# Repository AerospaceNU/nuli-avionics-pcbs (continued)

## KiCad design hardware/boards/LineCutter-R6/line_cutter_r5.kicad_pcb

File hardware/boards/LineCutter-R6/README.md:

# LineCutter-R6

Line cutter, revision 6 (project files are still named r5).

## Contributors

Patrick McGuire, zilinSi

## Status

**Version:** not recorded (the board's title block has no revision)
**Status:** Moved here from CADLab NULIAvionics/Line-Cutters-R6; this folder is now the working copy.

## Description

Line cutter, revision 6 (project files are still named r5).

- KiCad project: `line_cutter_r5.kicad_pro`, last saved with KiCad 7.0
- Schematic sheets: `line_cutter_r5.kicad_sch`, `storage.kicad_sch`, `power.kicad_sch`, `input_prot.kicad_sch`, `mcu.kicad_sch`, `sensors.kicad_sch`, `usb_hub.kicad_sch`, `pyros_servos.kicad_sch`, `pyro_chan.kicad_sch`
- Board size: 61.1 x 30.6 mm
- `fabrication/`: `assembly/`, `bom/`, `gerbers/`, `pick-and-place/`

## Manufacturing

- Layers: 4
- Thickness: 1.606 mm
- Surface finish: not set in the board stackup
- Minimum trace/space: 0.127 mm / 0.127 mm (smallest track on the board / default netclass clearance)
- Minimum drill: 0.305 mm (design rule)
- Manufacturer: not recorded

## Known Issues

- The schematic and PCB are out of sync: 21 parts have a different footprint on the PCB than in the schematic, and 23 schematic parts aren't on the PCB. Run Update PCB from Schematic before the next spin.
- Its library tables also point at `../fcb_v2_lib.kicad_sym` and `../fcb_footprints.pretty`, which weren't in the CADLab repo.

## Revision History

| Version | Date | Changes |
|---|---|---|
| - | 2024-12-06 | Moved into this repo from CADLab NULIAvionics/Line-Cutters-R6 (history from 2024-11-14 to 2024-12-06 stays there) |

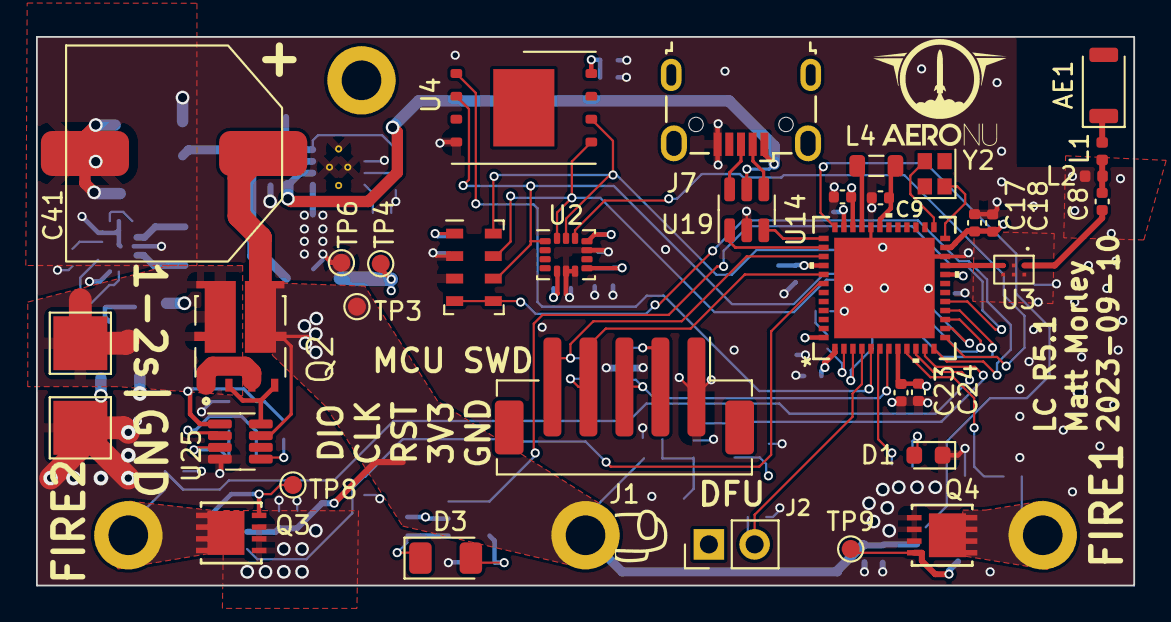
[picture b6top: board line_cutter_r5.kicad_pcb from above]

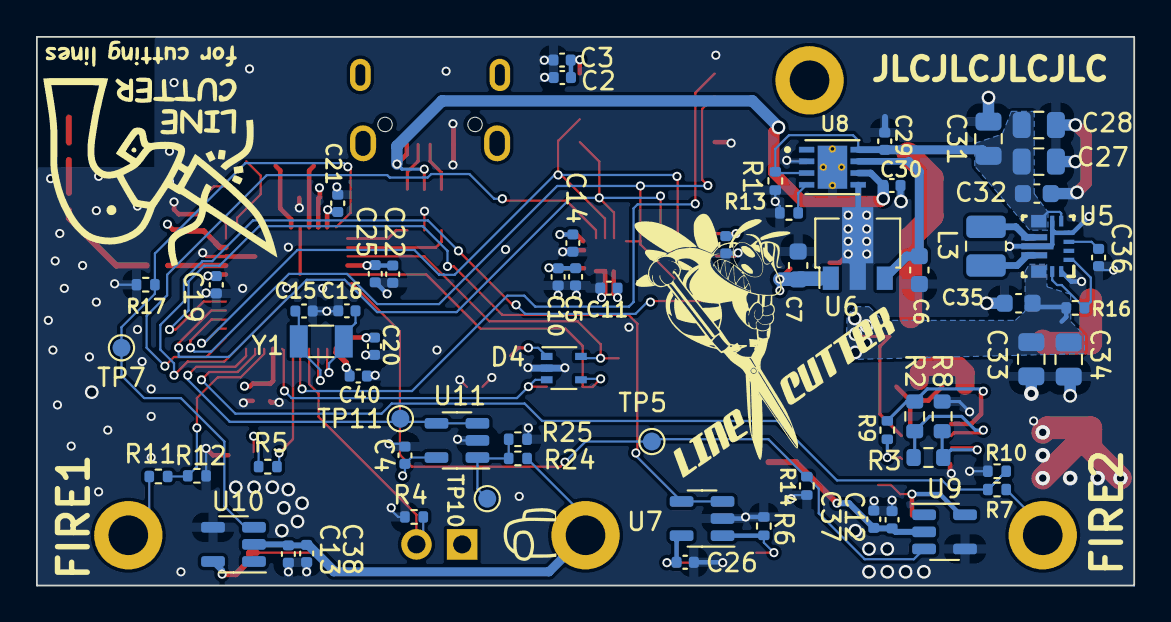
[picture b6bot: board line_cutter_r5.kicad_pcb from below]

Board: 4 copper layers, 61.0 x 30.5 mm, 104 parts (65 on the bottom side), 56 nets.

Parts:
AE1: 2450AT18B0100001E; Johanson_2450AT18x100_fixed
C1, C3, C4, C10, C12, C13, C14, C26, C29, C30, C36: 0.1u; C_0402_1005Metric
C2, C24, C37, C38: 1u; C_0402_1005Metric
C5: 2.2u; C_0402_1005Metric
C6: 1u; C_0603_1608Metric
C7: 4.7u; C_0603_1608Metric
C8: 1.2p; C_0402_1005Metric
C9, C22, C39: 4.7u; C_0402_1005Metric
C11, C23: 10n; C_0402_1005Metric
C15, C16: 15p; C_0402_1005Metric
C17, C19, C20, C21, C25, C40: 100n; C_0402_1005Metric
C18: 100p; C_0402_1005Metric
C27, C28, C31: 22u; C_0805_2012Metric
C32, C35: 10u; C_0603_1608Metric
C33, C34: 10u; C_0805_2012Metric
C41: 100m; FCS0H104ZFTBR24
D1: LED_Small; LED_0603_1608Metric
D3: PDB-C152SM; D_1206_3216Metric
D4: PESD3V3L4UG; SOT-353_SC-70-5
H1, H5, H6, H7: MountingHole_Pad; MountingHole_2.2mm_M2_DIN965_Pad
J1: Conn_01x05; JST_PH_B5B-PH-SM4-TB_1x05-1MP_P2.00mm_Vertical
J2: Conn_01x02_Female; PinHeader_1x02_P2.54mm_Vertical
J7: USB_B_Micro; USB_Micro-B_Wuerth_629105150521
L1: 3.3n; L_0402_1005Metric
L2: 2.7n; L_0402_1005Metric
L3: 1.5u; L_1008_2520Metric
L4: 2.2u; L_0805_2012Metric
Q2: SQJ974EP-T1_GE3; TRANS_SQJ974EP-T1_GE3
Q3, Q4: AON7528; DFN3X3A_8L_EPA1_P_AOS
R1, R10, R12, R14, R16, R17, R25: 10k; R_0402_1005Metric
R2: 320k; R_0603_1608Metric
R3: 270k; R_0603_1608Metric
R4, R9: 100k; R_0402_1005Metric
R5: 2k; R_0402_1005Metric
R6: 160k; R_0402_1005Metric
R7, R11, R24: 20k; R_0402_1005Metric
R8: 30k; R_0603_1608Metric
R13: 402R; R_0402_1005Metric
TP1, TP2: TestPoint; TestPoint_Pad_3.0x3.0mm
TP3, TP4, TP5, TP6, TP7, TP8, TP9, TP10, TP11: TestPoint; TestPoint_Pad_D1.0mm
U1: MS5607-02BA; LGA-8_3x5mm_P1.25mm
U2: ICM-20600; LGA-14_3x2.5mm_P0.5mm_LayoutBorder3x4y
U3: MLPF-WB55-01E3; MLPF-WB55-01E3_STM
U4: S25fl256lagnfi010; WSON-8-1EP_8x6mm_P1.27mm_EP3.4x4.3mm
U5: TPS630701RNMR; RNM0015A
U6: C50936; SOT-89-3
U7, U11: LMV321; SOT-23-5
U8: TPS2115ADRBR; SON65P300X300X100-9N
U9, U10: MCP1416; SOT-23-5
U14: STM32WB55CCU6TR; UFQFPN48-7x7mm
U19: USBLC6-2SC6; SOT-23-6
U25: LTC4365xTS8; TSOT-23-8
Y1: Q13FC1350000400; Crystal_SMD_3215-2Pin_3.2x1.5mm
Y2: ECS-320-8-37CKM; Crystal_SMD_2016-4Pin_2.0x1.6mm

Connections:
+3V3: C1.1, C2.2, C3.2, C4.1, C5.1, C7.1, C10.1, C11.1, C17.2, C18.2, C19.1, C20.1, C21.1, C22.1, C23.1, C24.1, C25.1, C26.1, C39.1, C40.2, D3.2 (A), D4.1 (K1), J1.2, J2.1, TP4.1, U1.1 (VDD), U2.5 (VDDIO), U2.8 (VDD), U4.8 (VCC), U6.1 (VOUT), U7.5 (V+), U11.5 (V+), U14.1 (VBAT), U14.8 (VDDA), U14.20 (VDD), U14.23 (VDDRF), U14.34 (VDDSMPS), U14.35 (VDD), U14.40 (VDDUSB), U14.48 (VDD)
+5V: C6.1, U6.3 (VIN), U8.7 (OUT)
/Main MCU/BARO1_CS: U1.4 (CSB), U1.5 (CSB), U14.12 (PA3)
/Main MCU/BOOT0: J2.2, R4.1, U14.4 (PH3-BOOT0)
/Main MCU/FCB_SWCLK: D4.4 (K3), J1.4, U14.41 (PA14)
/Main MCU/FCB_SWDIO: D4.5 (K4), J1.5, U14.39 (PA13)
/Main MCU/FIRE1_PWM: R17.2, TP7.1, U10.3 (IN), U14.36 (PA10)
/Main MCU/FIRE2_PWM: R14.2, TP5.1, U9.3 (IN), U14.42 (PA15)
/Main MCU/FLASH_CS: U4.1 (nCS), U14.5 (PB8)
/Main MCU/IMU1_CS: U2.12 (~CS), U14.13 (PA4)
/Main MCU/LIGHT_SENSE_BUF: U7.3 (-), U7.4, U14.17 (PA8)
/Main MCU/PYRO_SENSE_1: R11.1, R12.2, U14.9 (PA0)
/Main MCU/PYRO_SENSE_2: R7.1, R10.2, U14.10 (PA1)
/Main MCU/SPI_MISO: U1.6 (SDO), U2.1 (SDO/AD0), U4.2 (SO/IO1), U14.15 (PA6)
/Main MCU/SPI_MOSI: U1.7 (SDI/SDA), U2.14 (SDA/SDI), U4.5 (SI/IO0), U14.16 (PA7)
/Main MCU/SPI_SCK: U1.8 (SCLK), U2.13 (SCL/SCLK), U4.6 (SCK), U14.14 (PA5)
/Main MCU/STM_RF1_50R: U3.3 (IN), U14.21 (RF1)
/Main MCU/STM_RF2_50R: C8.1, U3.1 (OUT)
/Main MCU/STM_RF3_50R: C8.2, L1.2, L2.1
/Main MCU/STM_RF4_50R: AE1.1 (FEED), L1.1
/Main MCU/USB_D+: U14.38 (PA12), U19.1 (I/O1)
/Main MCU/USB_D-: U14.37 (PA11), U19.3 (I/O2)
/Main MCU/USER_LED: R5.2, U14.6 (PB9)
/Main MCU/VBATT_SENSE_IN: TP11.1, U11.3 (-), U11.4, U14.11 (PA2)
/Main MCU/nRST: D4.3 (K2), J1.3, U14.7 (NRST)
/Power Supplies/5V_BUCK-BOOST: C27.2, C28.2, C29.2, C31.2, C32.2, R1.1, U5.5 (FB), U5.7 (VOUT), U5.8 (VOUT), U8.3 (D1), U8.8 (IN1)
/Power Supplies/BATT_IN: C12.1, C13.1, C33.2, C34.2, C35.2, C37.1, C38.1, C41.1, H6.1, Q2.5, Q2.5_1, Q2.5_2, R16.2, R24.1, TP3.1, U5.12 (VIN), U5.13 (VIN), U9.2 (Vdd), U10.2 (Vdd), U25.7 (VOUT)
/Power Supplies/Input Protection/VIN: Q2.6, Q2.6_1, Q2.6_2, R2.2, R9.1, TP1.1, U25.1 (VIN)
/Power Supplies/USB_5V_IN: C30.2, J7.1 (VBUS), U8.6 (IN2), U19.5 (VBUS)
/Power Supplies/VBATT_SENSE: R24.2, R25.1, TP10.1, U11.1 (+)
/Pyros and Servos/PYRO1: H5.1, Q4.5 (D), Q4.6 (D), Q4.7 (D), Q4.8 (D), Q4.9 (D), R11.2
/Pyros and Servos/PYRO2: H7.1, Q3.5 (D), Q3.6 (D), Q3.7 (D), Q3.8 (D), Q3.9 (D), R7.2
/Pyros and Servos/Pyro Channel1/GATE: Q3.4 (G), TP8.1, U9.5 (OUT)
/Pyros and Servos/Pyro Channel/GATE: Q4.4 (G), TP9.1, U10.5 (OUT)
/USB Hub/UFP_D+: J7.3 (D+), U19.6 (I/O1)
/USB Hub/UFP_D-: J7.2 (D-), U19.4 (I/O2)
GND: C1.2, C2.1, C3.1, C4.2, C5.2, C6.2, C7.2, C9.2, C10.2, C11.2, C12.2, C13.2, C14.2, C15.1, C16.1, C17.1, C18.1, C19.2, C20.2, C21.2, C22.2, C23.2, C24.2, C25.2, C26.2, C27.1, C28.1, C29.1, C30.1, C31.1, C32.1, C33.1, C34.1, C35.1, C36.1, C37.2, C38.2, C39.2, C40.1, C41.2, D1.1 (K), D4.2 (A), J1.1, J7.5 (GND), L2.2, Q3.1 (S), Q3.2 (S), Q3.3 (S), Q4.1 (S), Q4.2 (S), Q4.3 (S), R1.2, R4.2, R6.2, R8.1, R10.1, R12.1, R13.1, R14.1, R17.1, R25.2, TP2.1, TP6.1, U1.2 (PS), U1.3 (GND), U2.6 (GND), U2.7 (RESV), U2.10 (FSYNC), U3.2 (GND), U3.4 (GND), U3.5 (GND), U3.6 (GND), U4.4 (GND), U5.4 (GND), U5.6 (FB2), U5.10 (PGND), U5.15 (VSEL), U6.2 (GND), U7.2 (V-), U8.2 (D0), U8.5 (GND), U8.9 (GND), U8.10 (GND), U9.4 (GND), U10.4 (GND), U11.2 (V-), U14.22 (VSSRF), U14.32 (VSSSMPS), U14.49 (EPAD), U19.2 (GND), U25.4 (GND)
unnamed: D1.2 (A), R5.1
unnamed: D3.1 (K), R6.1, U7.1 (+)
unnamed: Q2.1, Q2.3
unnamed: C14.1, U2.11 (REGOUT)
unnamed: R16.1, U5.1 (PS_SYNC), U5.14 (EN)
unnamed: L3.1, U5.11 (L1)
unnamed: L3.2, U5.9 (L2)
unnamed: C36.2, U5.3 (VAUX)
unnamed: R13.2, U8.4 (ILIM)
unnamed: U14.25 (OSC_IN), Y2.3
unnamed: U14.24 (OSC_OUT), Y2.1
unnamed: C16.2, U14.2 (PC14-OSC32_IN), Y1.1
unnamed: C15.2, U14.3 (PC15-OSC32_OUT), Y1.2
unnamed: C9.1, L4.2, U14.31 (VFBSMPS)
unnamed: L4.1, U14.33 (VLXSMPS)
unnamed: Q2.2, Q2.4, U25.8 (GATE)
unnamed: R3.1, R8.2, U25.3 (OV)
unnamed: R2.1, R3.2, U25.2 (UV)
unnamed: R9.2, U25.5 (~SHDN)

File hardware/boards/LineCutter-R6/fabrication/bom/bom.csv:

Designator,Footprint,Quantity,Value,LCSC Part #
AE1,Johanson_2450AT18x100_fixed,1,2450AT18B0100001E,
"C1, C10, C12, C13, C14, C26, C29, C3, C30, C36, C4",0402,11,0.1u,
"C11, C23",0402,2,10n,
"C15, C16",0402,2,15p,
"C17, C19, C20, C21, C25, C40",0402,6,100n,
C18,0402,1,100p,
"C2, C24, C37, C38",0402,4,1u,
"C22, C39, C9",0402,3,4.7u,
"C27, C28, C31",0805,3,22u,
"C32, C35",0603,2,10u,
"C33, C34",0805,2,10u,
C41,FCS0H104ZFTBR24,1,100m,
C5,0402,1,2.2u,
C6,0603,1,1u,
C7,0603,1,4.7u,
C8,0402,1,1.2p,
D1,0603,1,LED_Small,
D3,1206,1,PDB-C152SM,
D4,SOT-353_SC-70-5,1,PESD3V3L4UG,
"H1, H5, H6, H7",MountingHole_2.2mm_M2_DIN965_Pad,4,MountingHole_Pad,
J1,JST_PH_B5B-PH-SM4-TB_1x05-1MP_P2.00mm_Vertical,1,Conn_01x05,
J2,PinHeader_1x02_P2.54mm_Vertical,1,Conn_01x02_Female,
J7,USB_Micro-B_Wuerth_629105150521,1,USB_B_Micro,
L1,0402,1,3.3n,
L2,0402,1,2.7n,
L3,1008,1,1.5u,DFE252012F-1R5M=P2
L4,0805,1,2.2u,
Q2,TRANS_SQJ974EP-T1_GE3,1,SQJ974EP-T1_GE3,
"Q3, Q4",DFN3X3A_8L_EPA1_P_AOS,2,AON7528,
"R1, R10, R12, R14, R16, R17, R25",0402,7,10k,
"R11, R24, R7",0402,3,20k,
R13,0402,1,402R,
R2,0603,1,320k,
R3,0603,1,270k,
"R4, R9",0402,2,100k,
R5,0402,1,2k,
R6,0402,1,160k,
R8,0603,1,30k,
"TP1, TP2",TestPoint_Pad_3.0x3.0mm,2,TestPoint,
"TP10, TP11, TP3, TP4, TP5, TP6, TP7, TP8, TP9",TestPoint_Pad_D1.0mm,9,TestPoint,
U1,LGA-8_3x5mm_P1.25mm,1,MS5607-02BA,
"U10, U9",SOT-23-5,2,MCP1416,
"U11, U7",SOT-23-5,2,LMV321,
U14,UFQFPN48-7x7mm,1,STM32WB55CCU6TR,
U19,SOT-23-6,1,USBLC6-2SC6,
U2,LGA-14_3x2.5mm_P0.5mm_LayoutBorder3x4y,1,ICM-20600,
U25,TSOT-23-8,1,LTC4365xTS8,
U3,MLPF-WB55-01E3_STM,1,MLPF-WB55-01E3,
U4,WSON-8-1EP_8x6mm_P1.27mm_EP3.4x4.3mm,1,S25fl256lagnfi010,
U5,RNM0015A,1,TPS630701RNMR,
U6,SOT-89-3,1,C50936,
U8,SON65P300X300X100-9N,1,TPS2115ADRBR,
Y1,Crystal_SMD_3215-2Pin_3.2x1.5mm,1,Q13FC1350000400,
Y2,Crystal_SMD_2016-4Pin_2.0x1.6mm,1,ECS-320-8-37CKM,

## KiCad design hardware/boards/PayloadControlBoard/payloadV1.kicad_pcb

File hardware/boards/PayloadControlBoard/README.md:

# PayloadControlBoard

Payload control board V1.

## Contributors

Patrick McGuire, Riley Post

## Status

**Version:** not recorded (the board's title block has no revision)
**Status:** Moved here from CADLab NULIAvionics/Payload-Control-Board; this folder is now the working copy.

## Description

Payload control board V1.

- KiCad project: `payloadV1.kicad_pro`, last saved with KiCad 8.0
- Schematic sheets: `payloadV1.kicad_sch`
- Board size: 77.8 x 52.3 mm
- `3d-models/`: board STEP export
- `fabrication/`: `bom/`, `drill/`, `gerbers/`, `pick-and-place/`

## Manufacturing

- Layers: 4
- Thickness: 1.6 mm
- Surface finish: not set in the board stackup
- Minimum trace/space: 0.157 mm / 0.2 mm (smallest track on the board / default netclass clearance)
- Minimum drill: 0.3 mm (design rule)
- Manufacturer: JLCPCB (the fabrication outputs are JLCPCB's)

## Known Issues

- Its library tables point at another machine's folders, so KiCad warns about missing libraries; the symbols and footprints stored in the design still open fine, and the parts are in `hardware/common-components/`.

## Revision History

| Version | Date | Changes |
|---|---|---|
| - | 2025-05-23 | Moved into this repo from CADLab NULIAvionics/Payload-Control-Board (history from 2024-12-06 to 2025-05-23 stays there) |

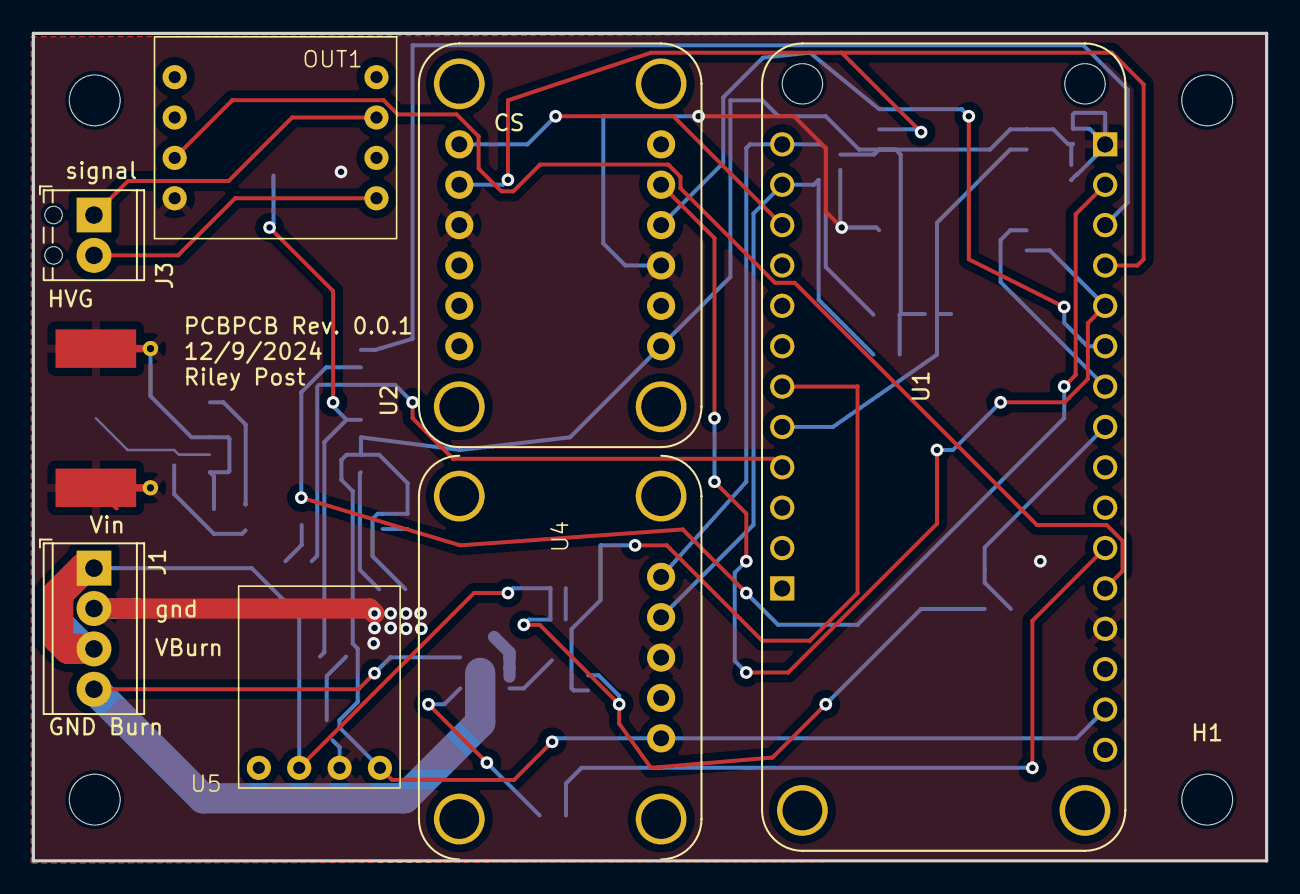
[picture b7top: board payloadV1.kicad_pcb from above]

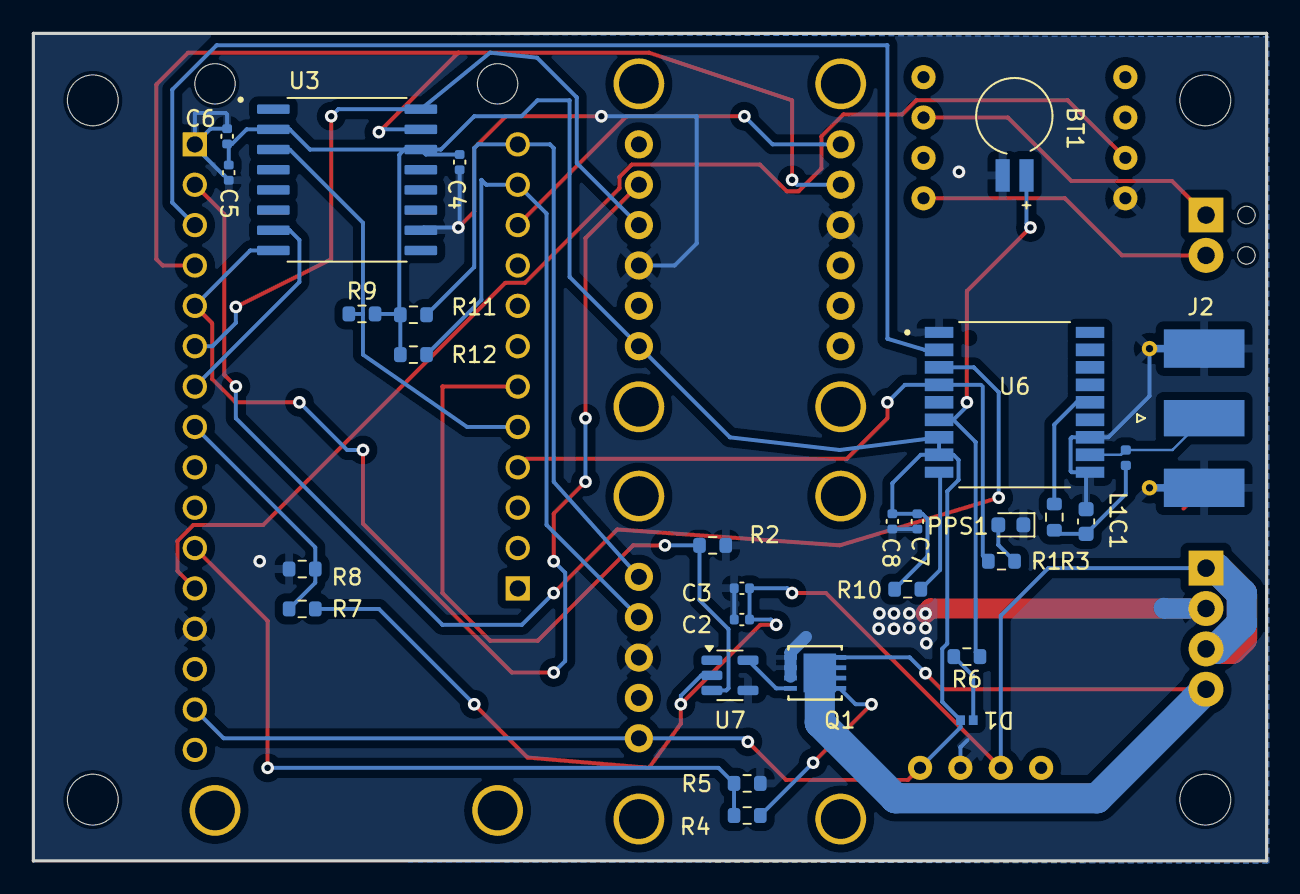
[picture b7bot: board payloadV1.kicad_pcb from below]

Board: 4 copper layers, 77.6 x 52.1 mm, 40 parts (29 on the bottom side), 29 nets.

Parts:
BT1: Battery_Cell; BAT_MS412FE-FL26E
C1: 10u; C_0603_1608Metric
C2, C5: 1u; C_0402_1005Metric
C3, C4, C6, C8: 0.1u; C_0402_1005Metric
C7: 10u; C_0402_1005Metric
D1: D; CFSH05-20L TR PBFREE_CNS
H1, H2, H3, H4: MountingHole; MountingHole_3.2mm_M3
J1: Screw_Terminal_01x04; TerminalBlock_Phoenix_MPT-0,5-4-2.54_1x04_P2.54mm_Horizontal
J2: Conn_Coaxial; SMA_Molex_73251-1153_EdgeMount_Horizontal
J3: Screw_Terminal_01x02; TerminalBlock_Phoenix_MPT-0,5-2-2.54_1x02_P2.54mm_Horizontal
L1: 27n; L_0402_1005Metric
PPS1: LED_Small; LED_0603_1608Metric
Q1: AON7528; DFN3X3A_8L_EPA1_P_AOS
R1: 2k; R_0603_1608Metric
R2, R5: 10k; R_0603_1608Metric
R3: 10; R_0603_1608Metric
R4: 20k; R_0603_1608Metric
R6: 3.3k; R_0603_1608Metric
R7, R9, R10: 56k; R_0603_1608Metric
R8: 4.3k; R_0603_1608Metric
R11, R12: R1; R_0603_1608Metric
U1: FEATHER_M0_BASIC_PROTO; MODULE_FEATHER_M0_BASIC_PROTO
U2: ICM20948; MODULE_ICM20948
U3: SOIC127P1030X265-16N
U4: MS8607
U5: D24V5F3
U6: MAX-M10S-00B; XCVR_MAX-M10S-00B
U7: MCP1416; SOT-23-5
U8: BOB-09118

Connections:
/GATE: Q1.4 (G), U7.5 (OUT)
/GPS_RF_IN: J2.1 (In), L1.1, U6.11 (RF_IN)
GND: BT1.2 (-), C1.2, C2.2, C3.2, C4.1, C5.1, C6.1, C7.1, C8.1, J1.2, J2.2 (Ext), PPS1.1 (K), Q1.1 (S), Q1.2 (S), Q1.3 (S), R2.1, R5.1, R8.2, U1.P1_1 (GND), U1.P1_13 (GND), U2.3 (GND), U2.9 (GND), U3.10 (VSS), U4.3 (GND), U5.2 (GND), U6.1 (GND), U6.10 (GND), U6.12 (GND), U7.4 (GND), U8.8 (GND)
unnamed: BT1.1 (+), R6.1, U6.6 (V_BCKP)
unnamed: C1.1, L1.2, R3.2
unnamed: C4.2, C5.2, C6.2, C7.2, C8.2, D1.2 (A), R9.2, R10.1, R11.1, R12.1, U1.P1_15 (3V3), U2.1 (VIN), U3.2 (VCC), U3.14 (VIO/RFU), U4.1 (Vin), U5.1 (VOUT), U6.7 (V_IO), U6.8 (VCC)
unnamed: D1.1 (K), R6.2
unnamed: C2.1, C3.1, J1.1, J1.3, R7.1, U5.3 (VIN), U7.2 (Vdd)
unnamed: J1.4, Q1.5 (D), Q1.6 (D), Q1.7 (D), Q1.8 (D), Q1.9 (D), R4.2
unnamed: J3.1, U8.2 (HV)
unnamed: J3.2, U8.4 (HVG)
unnamed: PPS1.2 (A), R1.1
unnamed: U1.P1_12 (AIN0/DAC/EINT/PA02), U8.7 (IN2)
unnamed: R4.1, R5.2, U1.P1_11 (AIN2/EINT/PB08)
unnamed: R7.2, R8.1, U1.P1_8 (AIN5/EINT/PA05)
unnamed: U1.P1_7 (AIN10/EINT/PB02), U3.7 (CS#)
unnamed: U1.P1_4 (MISO/I2C/PA12), U2.8 (SDO/ADR), U3.15 (SI/IO0)
unnamed: U1.P1_5 (MOSI/I2SMC/EINT/PB10), U2.5 (SDI/SDA), U3.8 (SO/IO1)
unnamed: U1.P2_10 (PA15/EINT), U2.7 (CS)
unnamed: R2.2, U1.P2_6 (PA16/EINT/I2C), U7.3 (IN)
unnamed: R1.2, U1.P2_4 (PA17/EINT/I2C), U6.4 (TIMEPULSE)
unnamed: R9.1, U1.P2_5 (PA19/EINT/I2SD0), U3.3 (RESET#/RFU)
unnamed: R11.2, U1.P2_12 (PA22/EINT/I2C/SDA), U4.5 (SDA)
unnamed: R12.2, U1.P2_11 (PA23/EINT/I2C/SCL), U4.4 (SCL)
unnamed: U1.P1_3 (RX/I2SF0/EINT/PA11), U6.2 (TXD)
unnamed: U1.P1_6 (SCK/I2SCL/EINT/PB11), U2.4 (SCK/SCL), U3.16 (SCK)
unnamed: U1.P1_2 (TX/I2SCK/EINT/PA10), U6.3 (RXD)
unnamed: R3.1, U6.14 (VCC_RF)
unnamed: R10.2, U6.9 (~RESET)

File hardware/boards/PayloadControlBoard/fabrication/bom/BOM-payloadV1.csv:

Comment,Designator,Footprint,LCSC
27n,L1,L_0402_1005Metric,C2041663
10,"R3,R6",R_0603_1608Metric,C25077
56k,R9,R_0603_1608Metric,
0.1u,C8,C_0402_1005Metric,
10u,C7,C_0402_1005Metric,
0.1u,C6,C_0402_1005Metric,
1u,C5,C_0402_1005Metric,
0.1u,C4,C_0402_1005Metric,
MountingHole,H1,MountingHole_3.2mm_M3,
MountingHole,H3,MountingHole_3.2mm_M3,
Screw_Terminal_01x02,J3,"TerminalBlock_Phoenix_MPT-0,5-2-2.54_1x02_P2.54mm_Horizontal",
MountingHole,H2,MountingHole_3.2mm_M3,
~,U5,D24V5F3,
MountingHole,H4,MountingHole_3.2mm_M3,
ICM20948,U2,MODULE_ICM20948,
FEATHER_M0_BASIC_PROTO,U1,MODULE_FEATHER_M0_BASIC_PROTO,
Screw_Terminal_01x04,J1,"TerminalBlock_Phoenix_MPT-0,5-4-2.54_1x04_P2.54mm_Horizontal",
~,U4,MS8607,
~,U8,BOB-09118,
Battery_Cell,BT1,BAT_MS412FE-FL26E,
10k,R5,R_0603_1608Metric,
20k,R4,R_0603_1608Metric,
R1,R12,R_0603_1608Metric,
R1,R11,R_0603_1608Metric,
1u,C2,C_0402_1005Metric,
Conn_Coaxial,J2,SMA_Molex_73251-1153_EdgeMount_Horizontal,
56k,R7,R_0603_1608Metric,
AON7528,Q1,DFN3X3A_8L_EPA1_P_AOS,
MCP1416,U7,SOT-23-5,
4.3k,R8,R_0603_1608Metric,
~,U3,SOIC127P1030X265-16N,
0.1u,C3,C_0402_1005Metric,
2k,R1,R_0603_1608Metric,
D,D1,CFSH05-20L TR PBFREE_CNS,
10k,R2,R_0603_1608Metric,
10u,C1,C_0603_1608Metric,
LED_Small,PPS1,LED_0603_1608Metric,
MAX-M10S-00B,U6,XCVR_MAX-M10S-00B,
56k,R10,R_0603_1608Metric,

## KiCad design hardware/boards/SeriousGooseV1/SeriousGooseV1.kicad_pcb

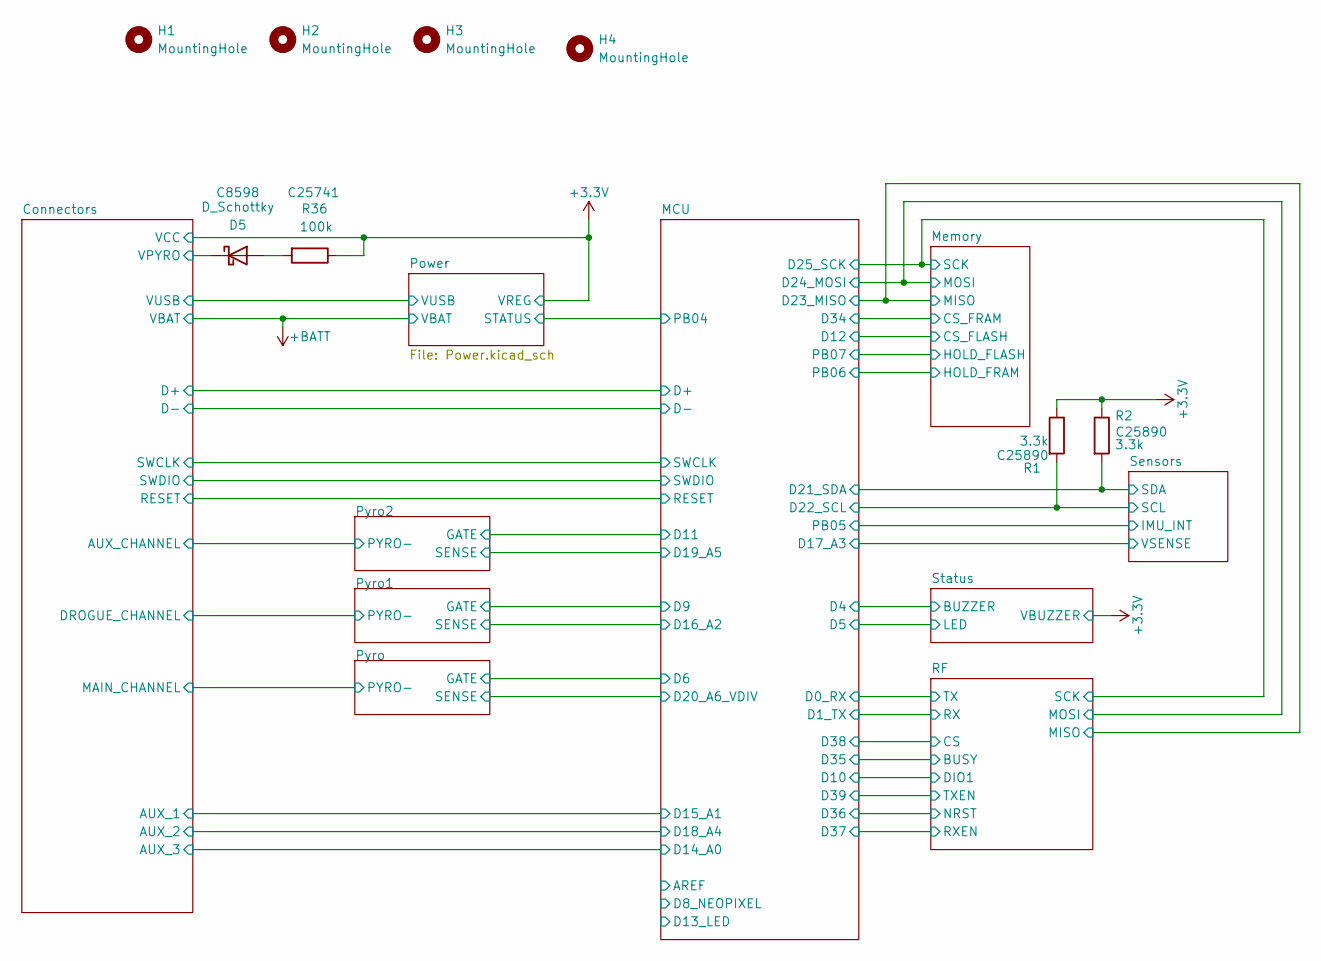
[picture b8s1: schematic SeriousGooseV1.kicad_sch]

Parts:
D5: D_Schottky; D_SOD-123; LCSC C8598
H1, H2, H3, H4: MountingHole; FixedMountingHole_2.5mm_Pad
R1, R2: 3.3k; R_0402_1005Metric; LCSC C25890
R36: 100k; R_0402_1005Metric; LCSC C25741

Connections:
+3.3V: R1.1, R2.1, R36.1; also elsewhere on the board
/Connectors/VPYRO: D5.1 (K); also elsewhere on the board
/MCU/D21_SDA: R2.2; also elsewhere on the board
/MCU/D22_SCL: R1.2; also elsewhere on the board
unnamed: D5.2 (A), R36.2

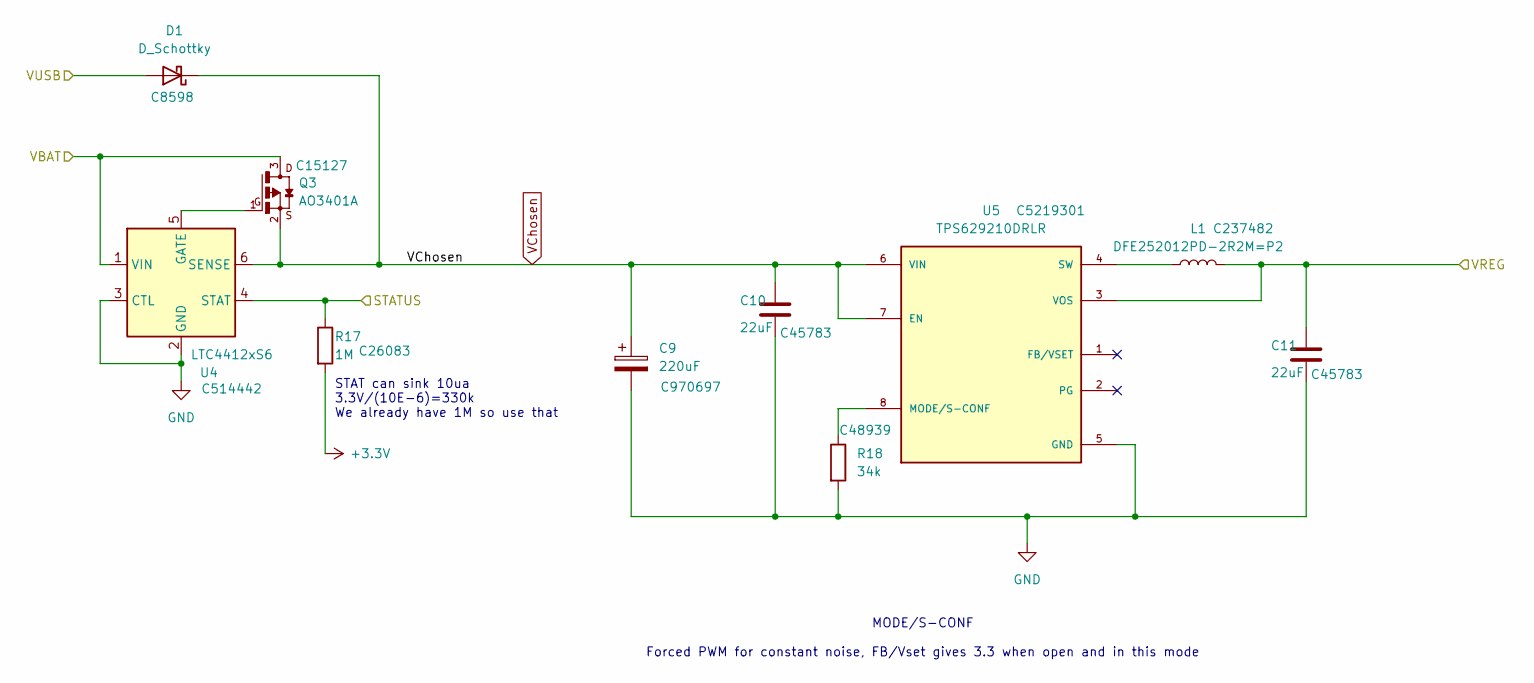
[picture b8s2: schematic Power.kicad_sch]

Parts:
C9: 220uF; CP_Elec_8x10.5; LCSC C970697
C10, C11: 22uF; C_0805_2012Metric; LCSC C45783
D1: D_Schottky; D_SOD-123; LCSC C8598
L1: DFE252012PD-2R2M=P2; L_1008_2520Metric; LCSC C237482
Q3: AO3401A; SSOT-3; LCSC C15127
R17: 1M; R_0402_1005Metric; LCSC C26083
R18: 34k; R_0402_1005Metric; LCSC C48939
U4: LTC4412xS6; TSOT-23-6; LCSC C514442
U5: TPS629210DRLR; SOT50P160X60-8N; PARTREV B; LCSC C5219301

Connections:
+3.3V: C11.1, L1.2, R17.2, U5.3 (VOS); also elsewhere on the board
+BATT: Q3.3, U4.1 (VIN); also elsewhere on the board
/Connectors/VUSB: D1.2 (A); also elsewhere on the board
/MCU/PB04: R17.1, U4.4 (STAT); also elsewhere on the board
GND: C9.2, C10.2, C11.2, R18.2, U4.2 (GND), U4.3 (CTL), U5.5 (GND); also elsewhere on the board
unnamed: Q3.1, U4.5 (GATE)
unnamed: R18.1, U5.8 (MODE/S-CONF)
unnamed: L1.1, U5.4 (SW)
VChosen: C9.1, C10.1, D1.1 (K), Q3.2, U4.6 (SENSE), U5.6 (VIN), U5.7 (EN); also elsewhere on the board

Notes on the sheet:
STAT can sink 10ua 3.3V/(10E-6)=330k We already have 1M so use that
MODE/S-CONF Forced PWM for constant noise, FB/Vset gives 3.3 when open and in this mode

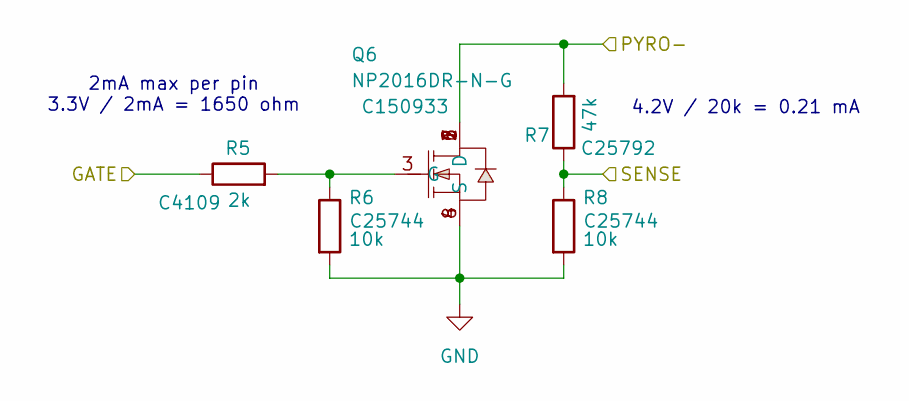
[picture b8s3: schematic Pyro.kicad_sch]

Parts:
Q6: NP2016DR-N-G; U-DFN2020-6; LCSC C150933
R5: 2k; R_0402_1005Metric; LCSC C4109
R6, R8: 10k; R_0402_1005Metric; LCSC C25744
R7: 47k; R_0402_1005Metric; LCSC C25792

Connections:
/Connectors/MAIN_CHANNEL: Q6.1 (D), Q6.2 (D), Q6.5 (D), Q6.6 (D), Q6.7 (D), R7.2; also elsewhere on the board
/MCU/D6: R5.1; also elsewhere on the board
/MCU/D20_A6_VDIV: R7.1, R8.1; also elsewhere on the board
GND: Q6.4 (S), Q6.8 (S), R6.2, R8.2; also elsewhere on the board
unnamed: Q6.3 (G), R5.2, R6.1

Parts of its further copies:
Q7, Q8: NP2016DR-N-G; U-DFN2020-6; LCSC C150933
R9, R27: 2k; R_0402_1005Metric; LCSC C4109
R10, R12, R28, R30: 10k; R_0402_1005Metric; LCSC C25744
R11, R29: 47k; R_0402_1005Metric; LCSC C25792

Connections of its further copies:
/Connectors/AUX_CHANNEL: Q8.1 (D), Q8.2 (D), Q8.5 (D), Q8.6 (D), Q8.7 (D), R29.2; also elsewhere on the board
/Connectors/DROGUE_CHANNEL: Q7.1 (D), Q7.2 (D), Q7.5 (D), Q7.6 (D), Q7.7 (D), R11.2; also elsewhere on the board
/MCU/D9: R9.1; also elsewhere on the board
/MCU/D11: R27.1; also elsewhere on the board
/MCU/D16_A2: R11.1, R12.1; also elsewhere on the board
/MCU/D19_A5: R29.1, R30.1; also elsewhere on the board
GND: Q7.4 (S), Q7.8 (S), Q8.4 (S), Q8.8 (S), R10.2, R12.2, R28.2, R30.2; also elsewhere on the board
unnamed: Q7.3 (G), R9.2, R10.1
unnamed: Q8.3 (G), R27.2, R28.1

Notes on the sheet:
2mA max per pin 3.3V / 2mA = 1650 ohm
4.2V / 20k = 0.21 mA

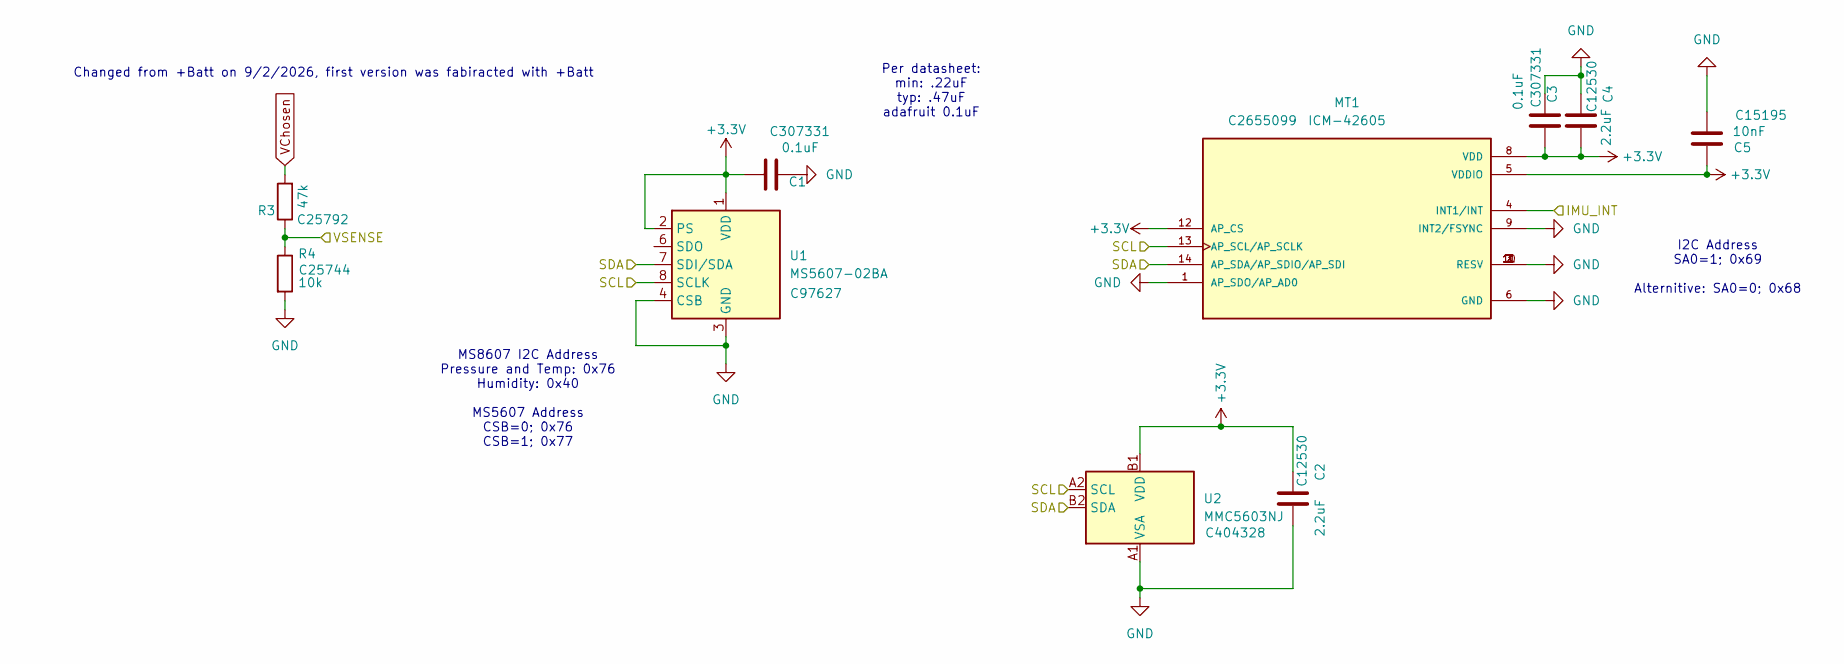
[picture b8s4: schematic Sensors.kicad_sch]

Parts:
C1, C3: 0.1uF; C_0402_1005Metric; LCSC C307331
C2, C4: 2.2uF; C_0402_1005Metric; LCSC C12530
C5: 10nF; C_0402_1005Metric; LCSC C15195
MT1: ICM-42605; XDCR_ICM-42605; PARTREV 1.7; LCSC C2655099
R3: 47k; R_0402_1005Metric; LCSC C25792
R4: 10k; R_0402_1005Metric; LCSC C25744
U1: MS5607-02BA; LGA-8_3x5mm_P1.25mm; LCSC C97627
U2: MMC5603NJ; WLP-4_0.86x0.86mm_P0.4mm; LCSC C404328

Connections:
+3.3V: C1.1, C2.2, C3.1, C4.1, C5.1, MT1.5 (VDDIO), MT1.8 (VDD), MT1.12 (AP_CS), U1.1 (VDD), U1.2 (PS), U2.B1 (VDD); also elsewhere on the board
/MCU/D17_A3: R3.1, R4.1; also elsewhere on the board
/MCU/D21_SDA: MT1.14 (AP_SDA/AP_SDIO/AP_SDI), U1.7 (SDI/SDA), U2.B2 (SDA); also elsewhere on the board
/MCU/D22_SCL: MT1.13 (AP_SCL/AP_SCLK), U1.8 (SCLK), U2.A2 (SCL); also elsewhere on the board
/MCU/PB05: MT1.4 (INT1/INT); also elsewhere on the board
GND: C1.2, C2.1, C3.2, C4.2, C5.2, MT1.1 (AP_SDO/AP_AD0), MT1.2 (RESV), MT1.3 (RESV), MT1.6 (GND), MT1.7 (RESV), MT1.9 (INT2/FSYNC), MT1.10 (RESV), MT1.11 (RESV), R4.2, U1.3 (GND), U1.4 (CSB), U1.5 (CSB), U2.A1 (VSA); also elsewhere on the board
VChosen: R3.2; also elsewhere on the board

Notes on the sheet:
MS8607 I2C Address Pressure and Temp: 0x76 Humidity: 0x40 MS5607 Address CSB=0; 0x76 CSB=1; 0x77
Changed from +Batt on 9/2/2026, first version was fabiracted with +Batt
Per datasheet: min: .22uF typ: .47uF adafruit 0.1uF
I2C Address SA0=1; 0x69 Alternitive: SA0=0; 0x68

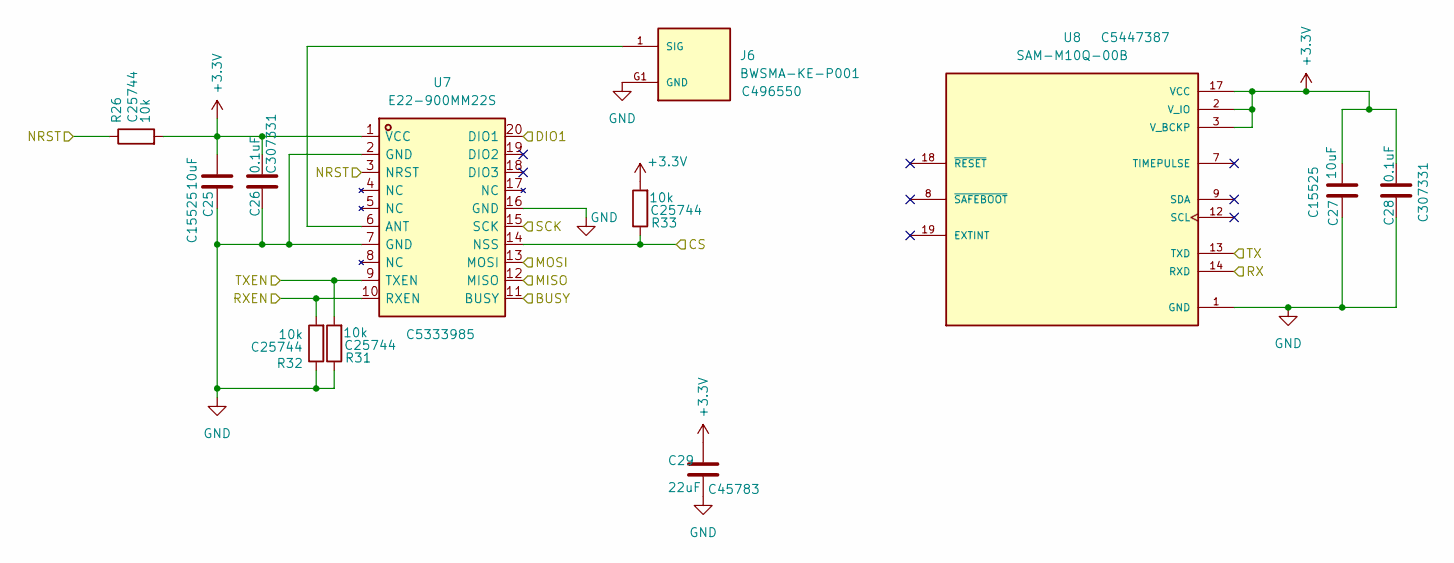
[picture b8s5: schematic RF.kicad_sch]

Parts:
C25, C27: 10uF; C_0402_1005Metric; LCSC C15525
C26, C28: 0.1uF; C_0402_1005Metric; LCSC C307331
C29: 22uF; C_0805_2012Metric; LCSC C45783
J6: BWSMA-KE-P001; BATWIRELESS_BWSMA-KE-P001; PARTREV A; LCSC C496550
R26, R31, R32, R33: 10k; R_0402_1005Metric; LCSC C25744
U7: E22-900MM22S; MPN E22-900MM22S; LCSC C5333985
U8: SAM-M10Q-00B; XCVR_SAM-M10Q-00B; PARTREV R03; LCSC C5447387

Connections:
+3.3V: C25.2, C26.1, C27.2, C28.1, C29.1, R26.2, R33.2, U7.1 (VCC), U8.2 (V_IO), U8.3 (V_BCKP), U8.17 (VCC); also elsewhere on the board
/MCU/D0_RX: U8.13 (TXD); also elsewhere on the board
/MCU/D1_TX: U8.14 (RXD); also elsewhere on the board
/MCU/D10: U7.20 (DIO1); also elsewhere on the board
/MCU/D23_MISO: U7.12 (MISO); also elsewhere on the board
/MCU/D24_MOSI: U7.13 (MOSI); also elsewhere on the board
/MCU/D25_SCK: U7.15 (SCK); also elsewhere on the board
/MCU/D35: U7.11 (BUSY); also elsewhere on the board
/MCU/D36: R26.1, U7.3 (NRST); also elsewhere on the board
/MCU/D37: R32.2, U7.10 (RXEN); also elsewhere on the board
/MCU/D38: R33.1, U7.14 (NSS); also elsewhere on the board
/MCU/D39: R31.2, U7.9 (TXEN); also elsewhere on the board
GND: C25.1, C26.2, C27.1, C28.2, C29.2, J6.G1 (GND), J6.G2 (GND), J6.G3 (GND), J6.G4 (GND), R31.1, R32.1, U7.2 (GND), U7.7 (GND), U7.16 (GND), U8.1 (GND), U8.4 (GND), U8.5 (GND), U8.6 (GND), U8.10 (GND), U8.11 (GND), U8.15 (GND), U8.16 (GND), U8.20 (GND); also elsewhere on the board
unnamed: J6.1 (SIG), U7.6 (ANT)
